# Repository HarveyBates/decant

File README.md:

# Decant

CAN-to-USB analyser. Designed to plug into existing CAN infrastructure for analysis. Focused on CANopen. UI is a work in progress.

## Hardware

<div>
  
</div>

### Electronics
- [x] STM32F4 based processor
- [x] Two CAN interfaces with MCP2562 trancievers
- [x] USB powered
- [ ] Breakout other pins for various other functions
- [ ] Reduce footprint

#### BOM
See [BOM](electronics/bom/decant.csv), roughly $40 AUD ($25 USD). Main cost is the processor, however, this is the lowest cost STM32 that features 
CAN and USB on seperate pins.

#### PCB
See `electronics/decant/gerber` for [gerber files](https://github.com/HarveyBates/decant/tree/main/electronics/decant/gerber) 
that can be zipped and uploaded to a PCB manufactuer of choice. Get a top layer stencil too as this will make assembly easier.

## UI

This is a work in progress, currently using [Qt](https://www.qt.io/). Below is a TODO list to make it more functional.

<div>
  
</div>

### Base functions
- [x] Read raw CAN messages to table
- [ ] Filter messages
- [ ] Watch message
- [ ] Inspect bits
- [ ] Inspect message
- [ ] Graph selected bytes

### Database
- [ ] Connect DB
- [ ] Log raw to database
- [ ] Log message to DB (select bytes)

### Grafana 
- [ ] Graph from DB

## Licence
HarveyBates/decant is licensed under the **GNU Affero General Public License v3.0**

Permissions of this strongest copyleft license are conditioned on making available complete source code of licensed works and modifications, which include larger works using a licensed work, under the same license. Copyright and license notices must be preserved. Contributors provide an express grant of patent rights. When a modified version is used to provide a service over a network, the complete source code of the modified version must be made available.

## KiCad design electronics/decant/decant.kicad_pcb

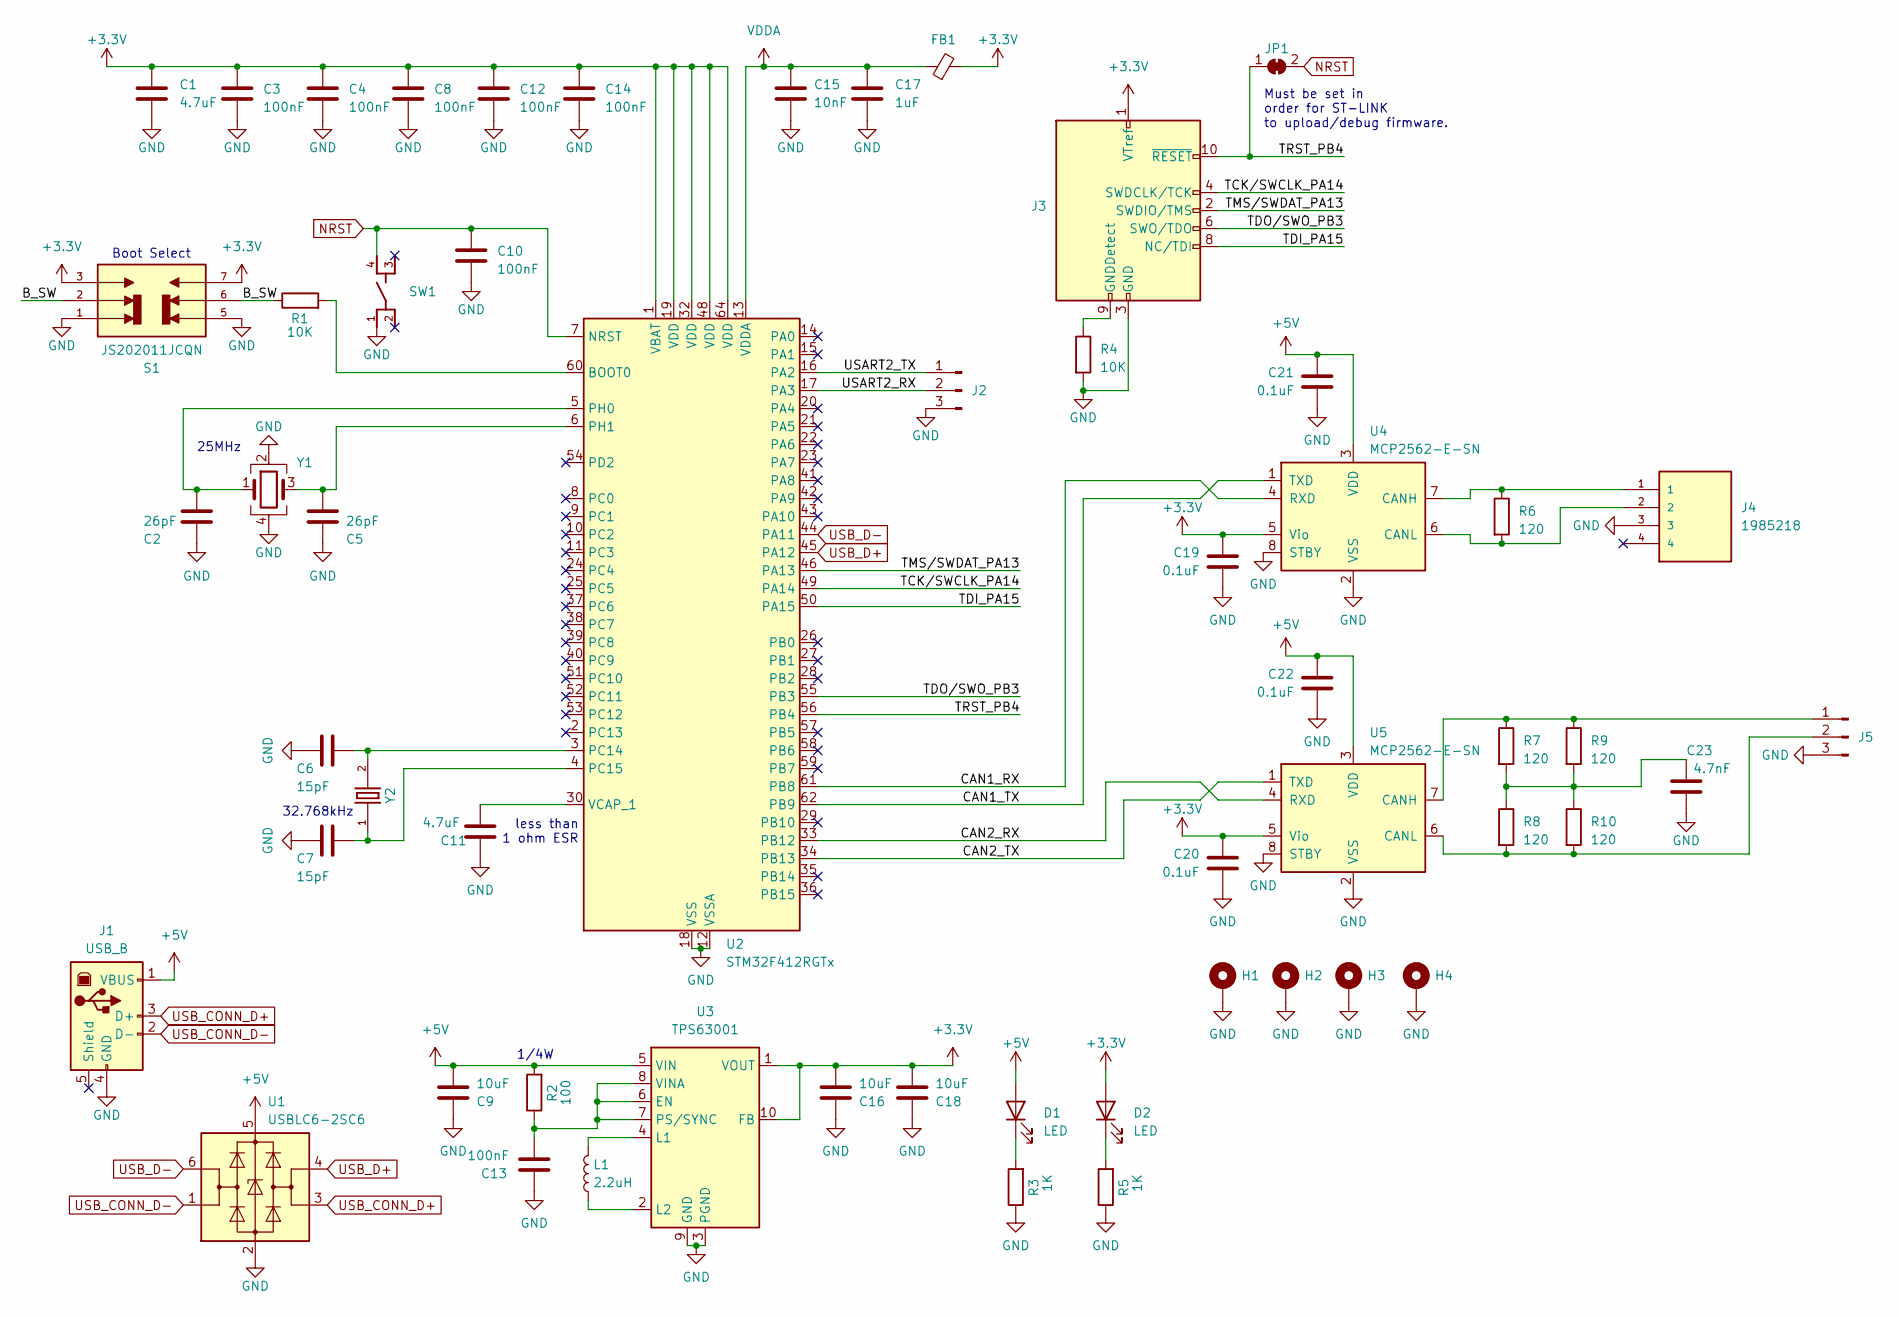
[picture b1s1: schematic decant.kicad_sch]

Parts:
C1, C11: 4.7uF; C_0805_2012Metric
C2, C5: 26pF; C_0805_2012Metric
C3, C4, C8, C10, C12, C13, C14: 100nF; C_0805_2012Metric
C6, C7: 15pF; C_0805_2012Metric
C9, C16, C18: 10uF; C_0805_2012Metric
C15: 10nF; C_0805_2012Metric
C17: 1uF; C_0805_2012Metric
C19, C20, C21, C22: 0.1uF; C_0805_2012Metric
C23: 4.7nF; C_0805_2012Metric
D1, D2: LED; LED_0805_2012Metric
FB1: FerriteBead_Small; R_0805_2012Metric
H1, H2, H3, H4: MountingHole_Pad; MountingHole_3.2mm_M3_ISO14580_Pad_TopBottom
J1: USB_B; UJ2-BH-1-TH
J2, J5: Conn_01x03_Pin; PinSocket_1x03_P2.54mm_Vertical
J3: Conn_ARM_JTAG_SWD_10; PinHeader_2x05_P1.27mm_Vertical; Part GRPB052VWVN-RC
J4: 1985218; PARTREV 29.03.2021
JP1: SolderJumper-2_P1.3mm_Bridged_Pad1.0x1.5mm
L1: 2.2uH; LQH3NPN2R2MJRL; Part LQH3NPN2R2MJRL
R1, R4: 10K; R_0805_2012Metric
R2: 100; R_0805_2012Metric
R3, R5: 1K; R_0805_2012Metric
R6, R7, R8, R9, R10: 120; R_0805_2012Metric
S1: JS202011JCQN; PARTREV 11 Nov 19
SW1: PTS810_SJM_250_SMTR_LFS
U1: USBLC6-2SC6; SOT-23-6
U2: STM32F412RGTx; LQFP-64_10x10mm_P0.5mm
U3: TPS63001; Texas_DRC0010J_ThermalVias
U4, U5: MCP2562-E-SN; SOIC-8_3.9x4.9mm_P1.27mm
Y1: Crystal_GND24; Crystal_SMD_3225-4Pin_3.2x2.5mm; Part TSX-3225 25.0000MF10P-C0
Y2: ECS-.327-12.5-34R-C-TR; PARTREV 2016

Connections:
+3.3V: C1.1, C3.1, C4.1, C8.1, C12.1, C14.1, C16.1, C18.1, C19.1, C20.1, D2.2 (A), FB1.2, J3.1 (VTref), S1.3, S1.7, U2.1 (VBAT), U2.19 (VDD), U2.32 (VDD), U2.48 (VDD), U2.64 (VDD), U3.1 (VOUT), U3.10 (FB), U4.5 (Vio), U5.5 (Vio)
+5V: C9.1, C21.1, C22.1, D1.2 (A), J1.1 (VBUS), R2.2, U1.5 (VBUS), U3.5 (VIN), U4.3 (VDD), U5.3 (VDD)
/B_SW: R1.1, S1.2, S1.6
/CAN1_RX: U2.61 (PB8), U4.4 (RXD)
/CAN1_TX: U2.62 (PB9), U4.1 (TXD)
/CAN2_RX: U2.33 (PB12), U5.4 (RXD)
/CAN2_TX: U2.34 (PB13), U5.1 (TXD)
/TCK/SWCLK_PA14: J3.4 (SWDCLK/TCK), U2.49 (PA14)
/TDI_PA15: J3.8 (NC/TDI), U2.50 (PA15)
/TDO/SWO_PB3: J3.6 (SWO/TDO), U2.55 (PB3)
/TMS/SWDAT_PA13: J3.2 (SWDIO/TMS), U2.46 (PA13)
/TRST_PB4: J3.10 (~RESET), JP1.1 (A), U2.56 (PB4)
/USART2_RX: J2.2, U2.17 (PA3)
/USART2_TX: J2.1, U2.16 (PA2)
GND: C1.2, C2.2, C3.2, C4.2, C5.2, C6.2, C7.2, C8.2, C9.2, C10.2, C11.2, C12.2, C13.2, C14.2, C15.2, C16.2, C17.2, C18.2, C19.2, C20.2, C21.2, C22.2, C23.2, H1.1, H2.1, H3.1, H4.1, J1.4 (GND), J2.3, J3.3 (GND), J3.5 (GND), J4.3, J5.3, R3.1, R4.2, R5.1, S1.1, S1.5, SW1.1, U1.2 (GND), U2.12 (VSSA), U2.18 (VSS), U2.31 (VSS), U2.47 (VSS), U2.63 (VSS), U3.3 (PGND), U3.9 (GND), U3.11 (PGND), U4.2 (VSS), U4.8 (STBY), U5.2 (VSS), U5.8 (STBY), Y1.2, Y1.4
NRST: C10.1, JP1.2 (B), SW1.4, U2.7 (NRST)
unnamed: C23.1, R7.2, R8.1, R9.2, R10.1
unnamed: D1.1 (K), R3.2
unnamed: D2.1 (K), R5.2
unnamed: J3.9 (GNDDetect), R4.1
unnamed: J5.1, R7.1, R9.1, U5.7 (CANH)
unnamed: J5.2, R8.2, R10.2, U5.6 (CANL)
unnamed: R1.2, U2.60 (BOOT0)
unnamed: C6.1, U2.3 (PC14), Y2.2
unnamed: C7.1, U2.4 (PC15), Y2.1
unnamed: C2.1, U2.5 (PH0), Y1.1
unnamed: C5.1, U2.6 (PH1), Y1.3
unnamed: C11.1, U2.30 (VCAP_1)
unnamed: C13.1, R2.1, U3.6 (EN), U3.7 (PS/SYNC), U3.8 (VINA)
unnamed: L1.2, U3.4 (L1)
unnamed: L1.1, U3.2 (L2)
unnamed: J4.1, R6.1, U4.7 (CANH)
unnamed: J4.2, R6.2, U4.6 (CANL)
USB_CONN_D+: J1.3 (D+), U1.3 (I/O2)
USB_CONN_D-: J1.2 (D-), U1.1 (I/O1)
USB_D+: U1.4 (I/O2), U2.45 (PA12)
USB_D-: U1.6 (I/O1), U2.44 (PA11)
VDDA: C15.1, C17.1, FB1.1, U2.13 (VDDA)

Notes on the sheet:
1/4W
less than 1 ohm ESR
25MHz
32.768kHz
Boot Select
Must be set in order for ST-LINK to upload/debug firmware.

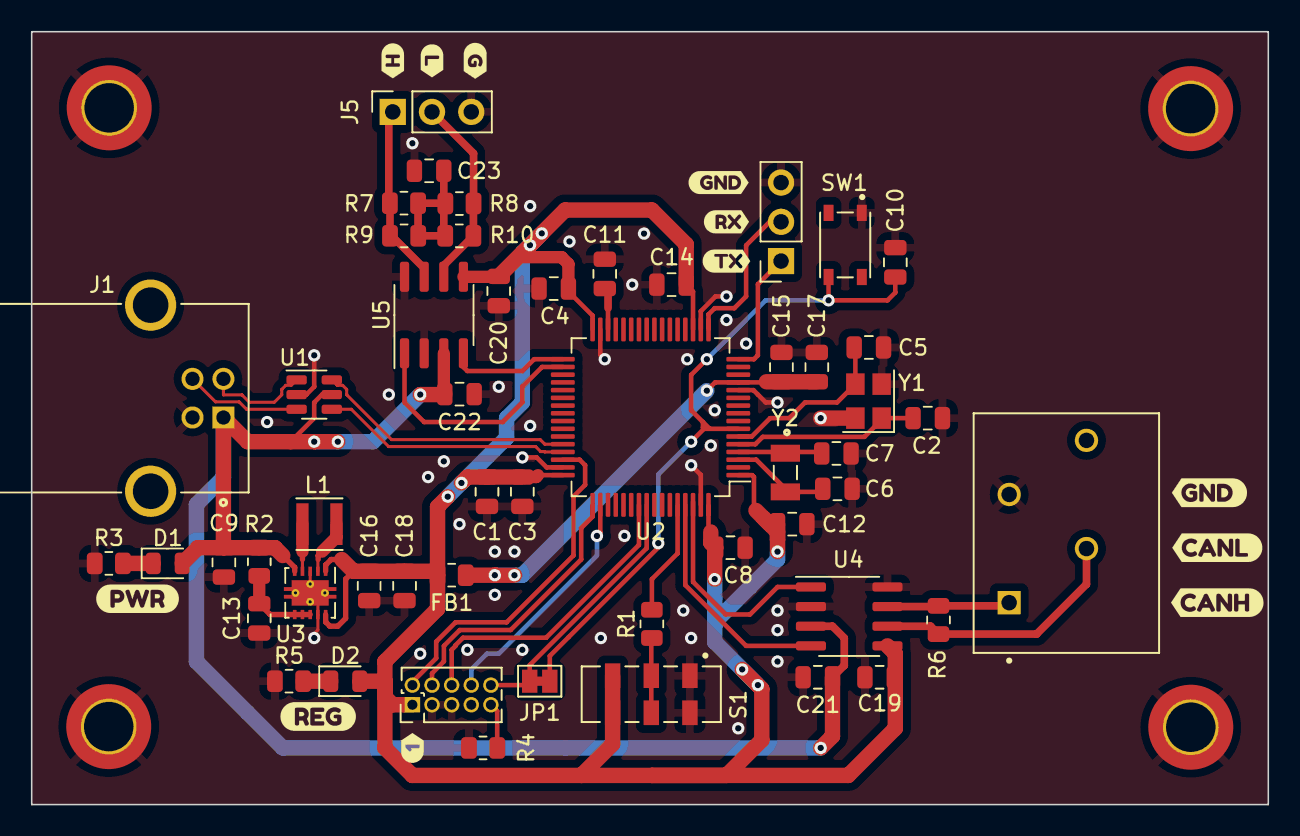
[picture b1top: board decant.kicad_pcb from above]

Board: 2 copper layers, 80.0 x 50.0 mm, 68 parts (0 on the bottom side), 38 nets.

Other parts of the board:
kibuzzard-6523D08B: G***; kibuzzard-6523D08B
kibuzzard-6523D09A: G***; kibuzzard-6523D09A
kibuzzard-6523D093: G***; kibuzzard-6523D093
kibuzzard-65247B4E: G***; kibuzzard-65247B4E
kibuzzard-65247B46: G***; kibuzzard-65247B46
kibuzzard-652479A8: G***; kibuzzard-652479A8
kibuzzard-652479B8: G***; kibuzzard-652479B8
kibuzzard-6524744D: G***; kibuzzard-6524744D
kibuzzard-6524799E: G***; kibuzzard-6524799E
kibuzzard-65247965: G***; kibuzzard-65247965
kibuzzard-65247981: G***; kibuzzard-65247981
kibuzzard-65247988: G***; kibuzzard-65247988

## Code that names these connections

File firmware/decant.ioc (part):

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Mcu.Name=STM32F412R(E-G)Tx
Mcu.Package=LQFP64
Mcu.UserName=STM32F412RGTx
PA11.Mode=Device_Only
PA11.Signal=USB_OTG_FS_DM
PA12.Mode=Device_Only
PA12.Signal=USB_OTG_FS_DP
PA13.Mode=JTAG_5_pins
PA13.Signal=SYS_JTMS-SWDIO
PA14.Mode=JTAG_5_pins
PA14.Signal=SYS_JTCK-SWCLK
PA15.Mode=JTAG_5_pins
PA15.Signal=SYS_JTDI
PA2.Mode=Asynchronous
PA2.Signal=USART2_TX
PA3.Mode=Asynchronous
PA3.Signal=USART2_RX
PB12.Mode=CAN_Activate
PB12.Signal=CAN2_RX
PB13.Mode=CAN_Activate
PB13.Signal=CAN2_TX
PB3.Mode=JTAG_5_pins
PB3.Signal=SYS_JTDO-SWO
PB4.Mode=JTAG_5_pins
PB4.Signal=SYS_JTRST
PB8.Mode=CAN_Activate
PB8.Signal=CAN1_RX
PB9.Mode=CAN_Activate
PB9.Signal=CAN1_TX
PC14-OSC32_IN.Mode=LSE-External-Oscillator
PC14-OSC32_IN.Signal=RCC_OSC32_IN
PC15-OSC32_OUT.Mode=LSE-External-Oscillator
PC15-OSC32_OUT.Signal=RCC_OSC32_OUT
PH0\ -\ OSC_IN.Mode=HSE-External-Oscillator
PH0\ -\ OSC_IN.Signal=RCC_OSC_IN
PH1\ -\ OSC_OUT.Mode=HSE-External-Oscillator
PH1\ -\ OSC_OUT.Signal=RCC_OSC_OUT
RCC.SYSCLKFreq_VALUE=16000000
board=custom

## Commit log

2023-10-26 initial commit with visu, firmware and electronics
2023-10-27 first messages being passed through and displayed. Added logging library (spdlog)
2023-11-04 switch from imgui to qt
2023-11-04 added filtered table, untested yet
2023-11-11 working on filtered table and bit inspector
2023-11-12 added media and models
2023-11-12 added bom
2023-11-12 Create LICENSE
